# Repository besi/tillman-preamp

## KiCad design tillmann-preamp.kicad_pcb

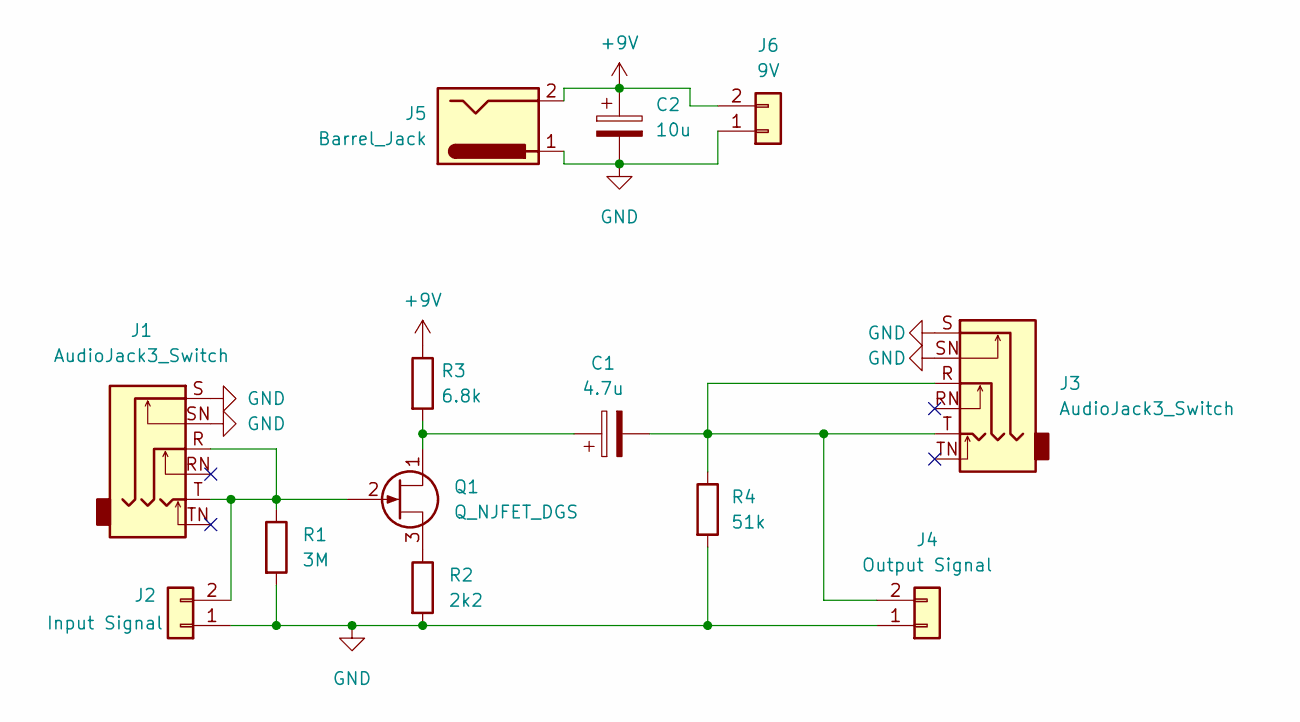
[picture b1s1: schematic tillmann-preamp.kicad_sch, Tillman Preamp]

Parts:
C1: 4.7u; CP_Radial_D5.0mm_P2.50mm
C2: 10u; CP_Radial_D5.0mm_P2.50mm
J1, J3: AudioJack3_Switch; Jack_6.35mm_Neutrik_NMJ6HFD2-AU_Horizontal
J2: Input Signal; PinHeader_1x02_P2.54mm_Vertical
J4: Output Signal; PinHeader_1x02_P2.54mm_Vertical
J5: Barrel_Jack; BarrelJack_CUI_PJ-063AH_Horizontal
J6: 9V; PinHeader_1x02_P2.54mm_Vertical
Q1: Q_NJFET_DGS; TO-92L_Inline_Wide
R1: 3M; R_Axial_DIN0204_L3.6mm_D1.6mm_P5.08mm_Vertical
R2: 2k2; R_Axial_DIN0204_L3.6mm_D1.6mm_P5.08mm_Vertical
R3: 6.8k; R_Axial_DIN0204_L3.6mm_D1.6mm_P2.54mm_Vertical
R4: 51k; R_Axial_DIN0204_L3.6mm_D1.6mm_P5.08mm_Vertical

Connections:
+9V: C2.1, J5.2, J6.2, R3.1
GND: C2.2, J1.S, J1.SN, J2.1, J3.S, J3.SN, J4.1, J5.1, J6.1, R1.2, R2.2, R4.2
unnamed: C1.1, Q1.1 (D), R3.2
unnamed: C1.2, J3.R, J3.T, J4.2, R4.1
unnamed: J1.R, J1.T, J2.2, Q1.2 (G), R1.1
unnamed: Q1.3 (S), R2.1

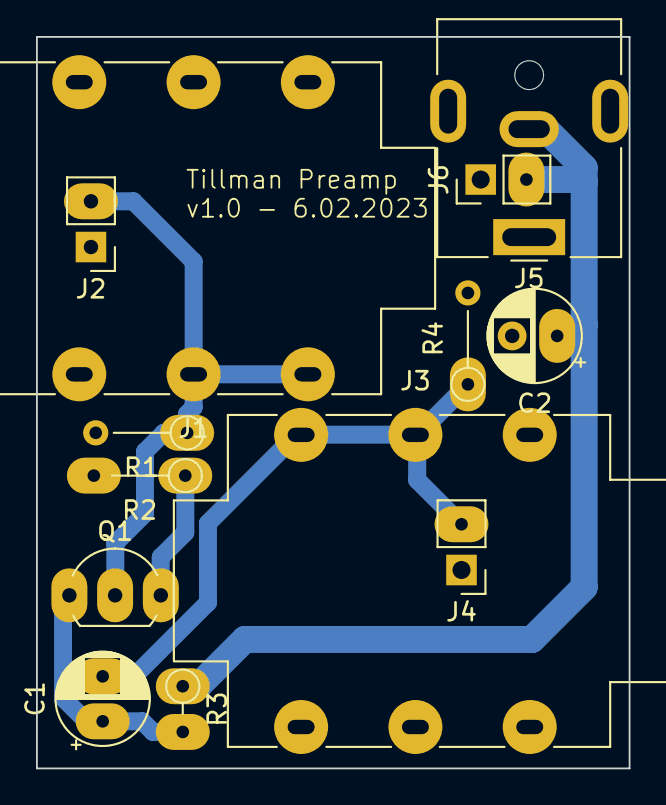
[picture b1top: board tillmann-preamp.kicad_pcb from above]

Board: 2 copper layers, 32.9 x 40.6 mm, 13 parts (0 on the bottom side), 6 nets.

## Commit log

2023-02-05 Initial schematic and design of tillman preamp
